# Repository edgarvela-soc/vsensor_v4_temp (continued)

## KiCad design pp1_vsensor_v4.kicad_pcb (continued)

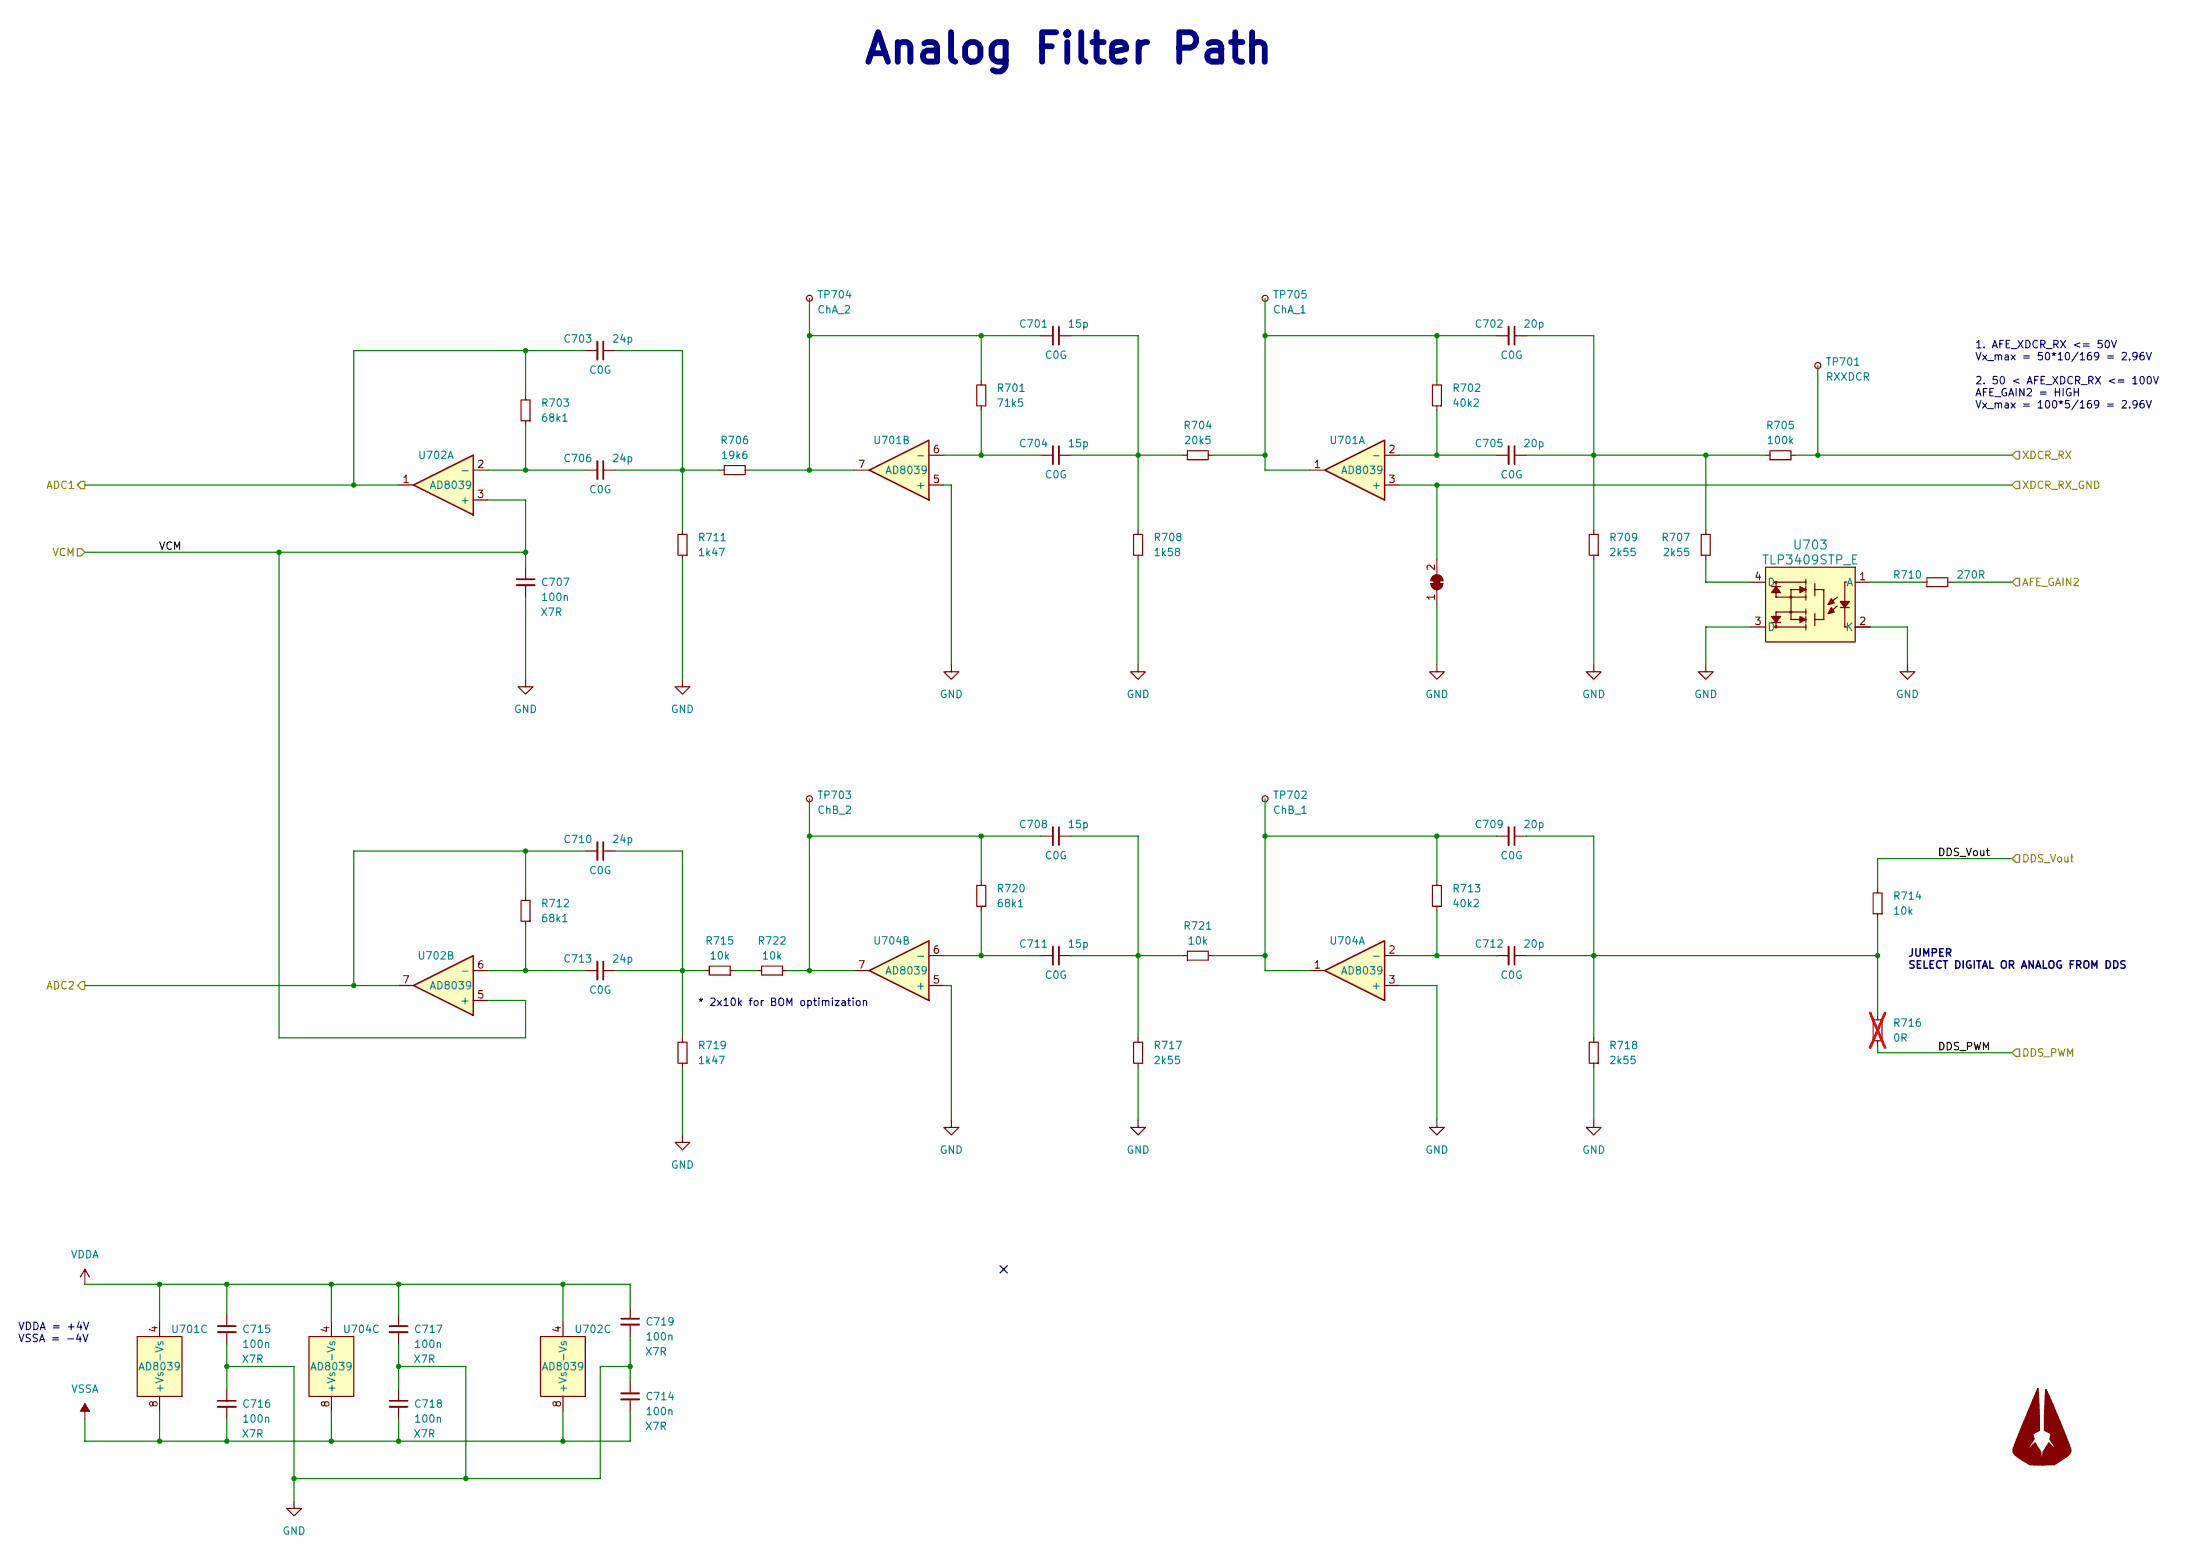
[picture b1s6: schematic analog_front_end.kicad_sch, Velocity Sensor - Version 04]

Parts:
C701, C704, C708, C711: 15p; C_0402_1005Metric; MPN CC0402JRNPO9BN150; Digikey_PN 311-1017-1-ND
C702, C705, C709, C712: 20p; C_0402_1005Metric; MPN CC0402JRNPO9BN200; Digikey_PN 311-1417-1-ND
C703, C706, C710, C713: 24p; C_0402_1005Metric; MPN CC0402JRNPO9BN240; Digikey_PN 311-1348-1-ND
C707, C714, C715, C716, C717, C718, C719: 100n; C_0402_1005Metric; Voltage 50V; MPN CC0402KRX7R9BB104; Digikey_PN 311-3566-1-ND
JP701: Bridged; NetTie-2_SMD_Pad0.5mm
Logo701: LOGO_AGU; AGU_15mm
R701: 71k5; R_0402_1005Metric; MPN RC0402FR-0771K5L; Digikey_PN YAG3222CT-ND
R702, R713: 40k2; R_0402_1005Metric; MPN RC0402FR-0740K2L; Digikey_PN 311-40.2KLRCT-ND
R703, R712, R720: 68k1; R_0402_1005Metric; MPN RC0402FR-0768K1L; Digikey_PN YAG3213CT-ND
R704: 20k5; R_0402_1005Metric; MPN RC0402FR-0720K5L; Digikey_PN YAG3052CT-ND
R705: 100k; R_0603_1608Metric; MPN RC0402FR-07100KL; Digikey_PN 311-100KLRCT-ND
R706: 19k6; R_0402_1005Metric; MPN RC0402FR-0719K6L; Digikey_PN YAG3026CT-ND
R707, R709, R717, R718: 2k55; R_0402_1005Metric; MPN RC0402FR-072K55L; Digikey_PN YAG3102CT-ND
R708: 1k58; R_0402_1005Metric; MPN RC0402FR-071K58L; Digikey_PN YAG3041CT-ND
R710: 270R; R_0402_1005Metric; MPN RMCF0402FT270R; Digikey_PN RMCF0402FT270RCT-ND
R711, R719: 1k47; R_0402_1005Metric; MPN RC0402FR-071K47L; Digikey_PN YAG3038CT-ND
R714, R715, R721, R722: 10k; R_0402_1005Metric; MPN RC1005F103CS; Digikey_PN 1276-3431-1-ND
R716: 0R; R_0402_1005Metric; MPN RC0402JR-070RL; Digikey_PN 311-0.0JRCT-ND; not fitted
TP701: RXXDCR; TestPoint_Pad_D1.0mm
TP702: ChB_1; TestPoint_Pad_D1.0mm
TP703: ChB_2; TestPoint_Pad_D1.0mm
TP704: ChA_2; TestPoint_Pad_D1.0mm
TP705: ChA_1; TestPoint_Pad_D1.0mm
U701, U702, U704: AD8039; SOT-23-8; MPN AD8039ARTZ-REEL7; Digikey_PN 505-AD8039ARTZ-REEL7CT-ND
U703: TLP3409STP_E; MPN TLP3409S(TP,E; Mouser_PN 757-TLP3409STPE

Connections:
/ADC/ADC1: C703.2, R703.2, U702.1; also elsewhere on the board
/ADC/ADC2: C710.2, R712.2, U702.7; also elsewhere on the board
/ADC/VCM: C707.1, U702.3 (+), U702.5 (+); also elsewhere on the board
/Analog Frontend/DDS_PWM: R716.1; also elsewhere on the board
/Analog Frontend/DDS_Vout: R714.2; also elsewhere on the board
/Microcontroller/AFE_GAIN2: R710.2; also elsewhere on the board
/Transducer Multiplexer/MUX_XDCR: R705.2, TP701.1; also elsewhere on the board
unnamed: C701.1, C704.1, R704.1, R708.2
unnamed: C701.2, R701.2, R706.2, TP704.1, U701.7
unnamed: C702.1, C705.1, R705.1, R707.2, R709.2
unnamed: C702.2, R702.2, R704.2, TP705.1, U701.1
unnamed: C703.1, C706.1, R706.1, R711.2
unnamed: C708.1, C711.1, R717.2, R721.1
unnamed: C708.2, R720.2, R722.1, TP703.1, U704.7
unnamed: C709.1, C712.1, R714.1, R716.2, R718.2
unnamed: C709.2, R713.2, R721.2, TP702.1, U704.1
unnamed: C710.1, C713.1, R715.2, R719.2
unnamed: R707.1, U703.4 (D)
unnamed: R715.1, R722.2
unnamed: C705.2, R702.1, U701.2 (-)
unnamed: C704.2, R701.1, U701.6 (-)
unnamed: C706.2, R703.1, U702.2 (-)
unnamed: C713.2, R712.1, U702.6 (-)
unnamed: R710.1, U703.1 (A)
unnamed: C712.2, R713.1, U704.2 (-)
unnamed: C711.2, R720.1, U704.6 (-)
VDDA: C715.1, C717.1, C719.1, U701.4 (-Vs), U702.4 (-Vs), U704.4 (-Vs); also elsewhere on the board
VSSA: C714.2, C716.2, C718.2, U701.8 (+Vs), U702.8 (+Vs), U704.8 (+Vs); also elsewhere on the board

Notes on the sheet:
1. AFE_XDCR_RX <= 50V Vx_max = 50*10/169 = 2.96V 2. 50 < AFE_XDCR_RX <= 100V AFE_GAIN2 = HIGH Vx_max = 100*5/169 = 2.96V
JUMPER SELECT DIGITAL OR ANALOG FROM DDS
* 2x10k for BOM optimization
VDDA = +4V VSSA = -4V
Analog Filter Path

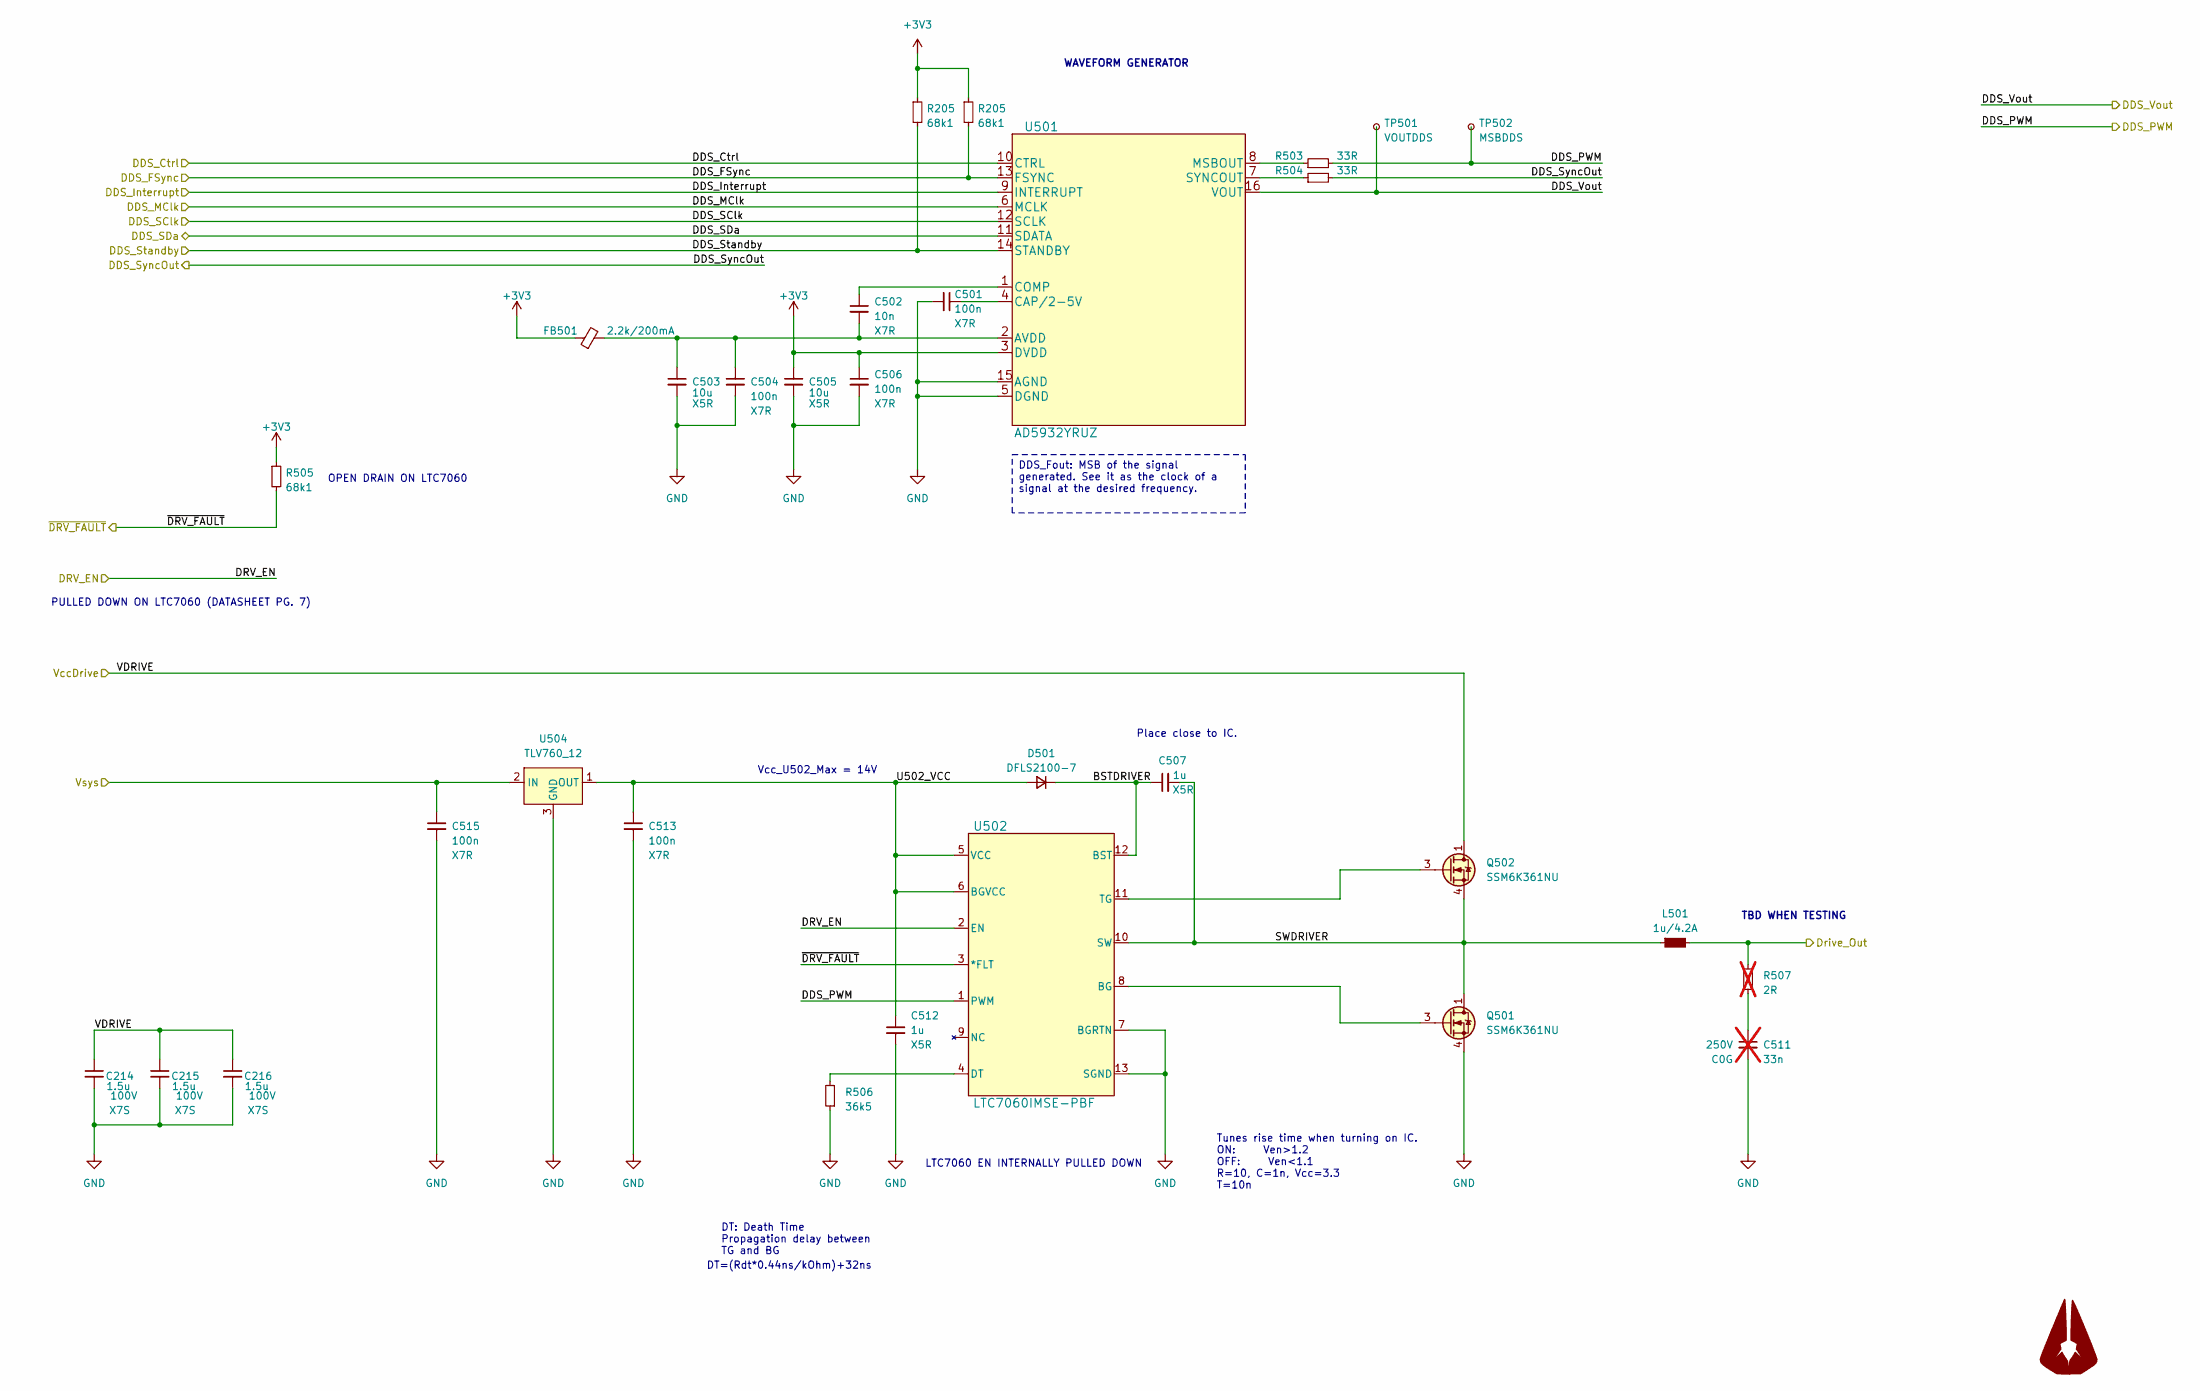
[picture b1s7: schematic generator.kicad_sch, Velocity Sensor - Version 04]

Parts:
C214, C215, C216: 1.5u; C_1206_3216Metric; Voltage 100V; MPN C3216X7S2A155K160AB; Mouser_PN 810-C3216X7S2A155K1B
C501, C504, C506, C513, C515: 100n; C_0402_1005Metric; Voltage 50V; MPN CC0402KRX7R9BB104; Digikey_PN 311-3566-1-ND
C502: 10n; C_0402_1005Metric; Voltage 50V; MPN GCM155R71H103KA55D; Digikey_PN 399-C0402C222J5RAC7867CT-ND
C503, C505: 10u; C_0603_1608Metric; Voltage 25V; MPN GRM188R61E106MA73D; Mouser_PN 81-GRM188R61E106MA3D
C507, C512: 1u; C_0402_1005Metric; Voltage 50V; MPN UMK105CBJ105MV-F; Digikey_PN 587-6278-1-ND
C511: 33n; C_0805_2012Metric; Voltage 250V; MPN 885342206005; Digikey_PN 732-12160-1-ND; not fitted
D501: DFLS2100-7; D_PowerDI-123; MPN DFLS2100-7; Mouser_PN 621-DFLS2100-7
FB501: 2.2k/200mA; L_0805_2012Metric; MPN 742792093; Digikey_PN 732-1609-1-ND
L501: 1u/4.2A; RES_CIGT201610; MPN CIGT201610EH1R0MNE; Digikey_PN 1276-6900-1-ND
Logo501: LOGO_AGU; AGU_15mm
Q501, Q502: SSM6K361NU; UDFN6B_TOS; MPN SSM6K361NU,LF; Digikey_PN SSM6K361NULFCT-ND
R205, R505: 68k1; R_0402_1005Metric; MPN RC0402FR-0768K1L; Digikey_PN YAG3213CT-ND
R503, R504: 33R; R_0402_1005Metric; MPN RC0402JR-0733RL; Digikey_PN 311-33JRCT-ND
R506: 36k5; R_0402_1005Metric; MPN ERJ-2RKF3652X; Digikey_PN P36.5KLCT-ND
R507: 2R; R_0805_2012Metric; MPN RMCF0603FT2R00; Digikey_PN RMCF0603FT2R00CT-ND; not fitted
TP501: VOUTDDS; TestPoint_Pad_D1.0mm
TP502: MSBDDS; TestPoint_Pad_D1.0mm
U501: AD5932YRUZ; MPN AD5932YRUZ; Mouser_PN 584-AD5932YRUZ
U502: LTC7060IMSE-PBF; LTC7060; MPN LTC7060IMSE#WTRPBF; Mouser_PN 584-7060IMSE#WTRPBF
U504: TLV760_12; SOT-23; MPN TLV76012DBZR; Digikey_PN 296-48331-1-ND

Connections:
+3V3: C505.1, C506.1, FB501.1, R505.1, U501.3 (DVDD); also elsewhere on the board
/Analog Frontend/DDS_PWM: R503.2, TP502.1, U502.1 (PWM); also elsewhere on the board
/Analog Frontend/DDS_Vout: TP501.1, U501.16 (VOUT); also elsewhere on the board
/Microcontroller/DDS_Ctrl: U501.10 (CTRL); also elsewhere on the board
/Microcontroller/DDS_FSync: U501.13 (FSYNC); also elsewhere on the board
/Microcontroller/DDS_INTERRUPT: U501.9 (INTERRUPT); also elsewhere on the board
/Microcontroller/DDS_MClk: U501.6 (MCLK); also elsewhere on the board
/Microcontroller/DDS_SClk: U501.12 (SCLK); also elsewhere on the board
/Microcontroller/DDS_SYNCOUT: R504.2; also elsewhere on the board
/Microcontroller/DDS_Sda: U501.11 (SDATA); also elsewhere on the board
/Microcontroller/DDS_Standby: U501.14 (STANDBY); also elsewhere on the board
/Microcontroller/DRIVE_EN: U502.2 (EN); also elsewhere on the board
/Microcontroller/~DRV_FAULT: R505.2, U502.3 (*FLT); also elsewhere on the board
/Signal Generator/BSTDRIVER: C507.1, D501.1 (K), U502.12 (BST)
/Signal Generator/SWDRIVER: C507.2, L501.1, Q501.1 (D), Q501.2 (D), Q501.5 (D), Q501.6 (D), Q501.7 (D), Q502.4 (S), Q502.8 (S), U502.10 (SW)
/Signal Generator/U502_VCC: C512.1, C513.1, D501.2 (A), U502.5 (VCC), U502.6 (BGVCC), U504.1 (OUT)
/Transducer Multiplexer/MUX_XDCR: L501.2, R507.2; also elsewhere on the board
unnamed: C511.1, R507.1
unnamed: Q501.3 (G), U502.8 (BG)
unnamed: Q502.3 (G), U502.11 (TG)
unnamed: C502.2, C503.1, C504.1, FB501.2, U501.2 (AVDD)
unnamed: C501.1, U501.4 (CAP/2-5V)
unnamed: C502.1, U501.1 (COMP)
unnamed: R503.1, U501.8 (MSBOUT)
unnamed: R504.1, U501.7 (SYNCOUT)
unnamed: R506.2, U502.4 (DT)

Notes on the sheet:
DDS_Fout: MSB of the signal generated. See it as the clock of a signal at the desired frequency.
Place close to IC.
Tunes rise time when turning on IC. ON: Ven>1.2 OFF: Ven<1.1 R=10, C=1n, Vcc=3.3 T=10n
OPEN DRAIN ON LTC7060
TBD WHEN TESTING
LTC7060 EN INTERNALLY PULLED DOWN
WAVEFORM GENERATOR
DT=(Rdt*0.44ns/kOhm)+32ns
PULLED DOWN ON LTC7060 (DATASHEET PG. 7)
DT: Death Time Propagation delay between TG and BG
Vcc_U502_Max = 14V

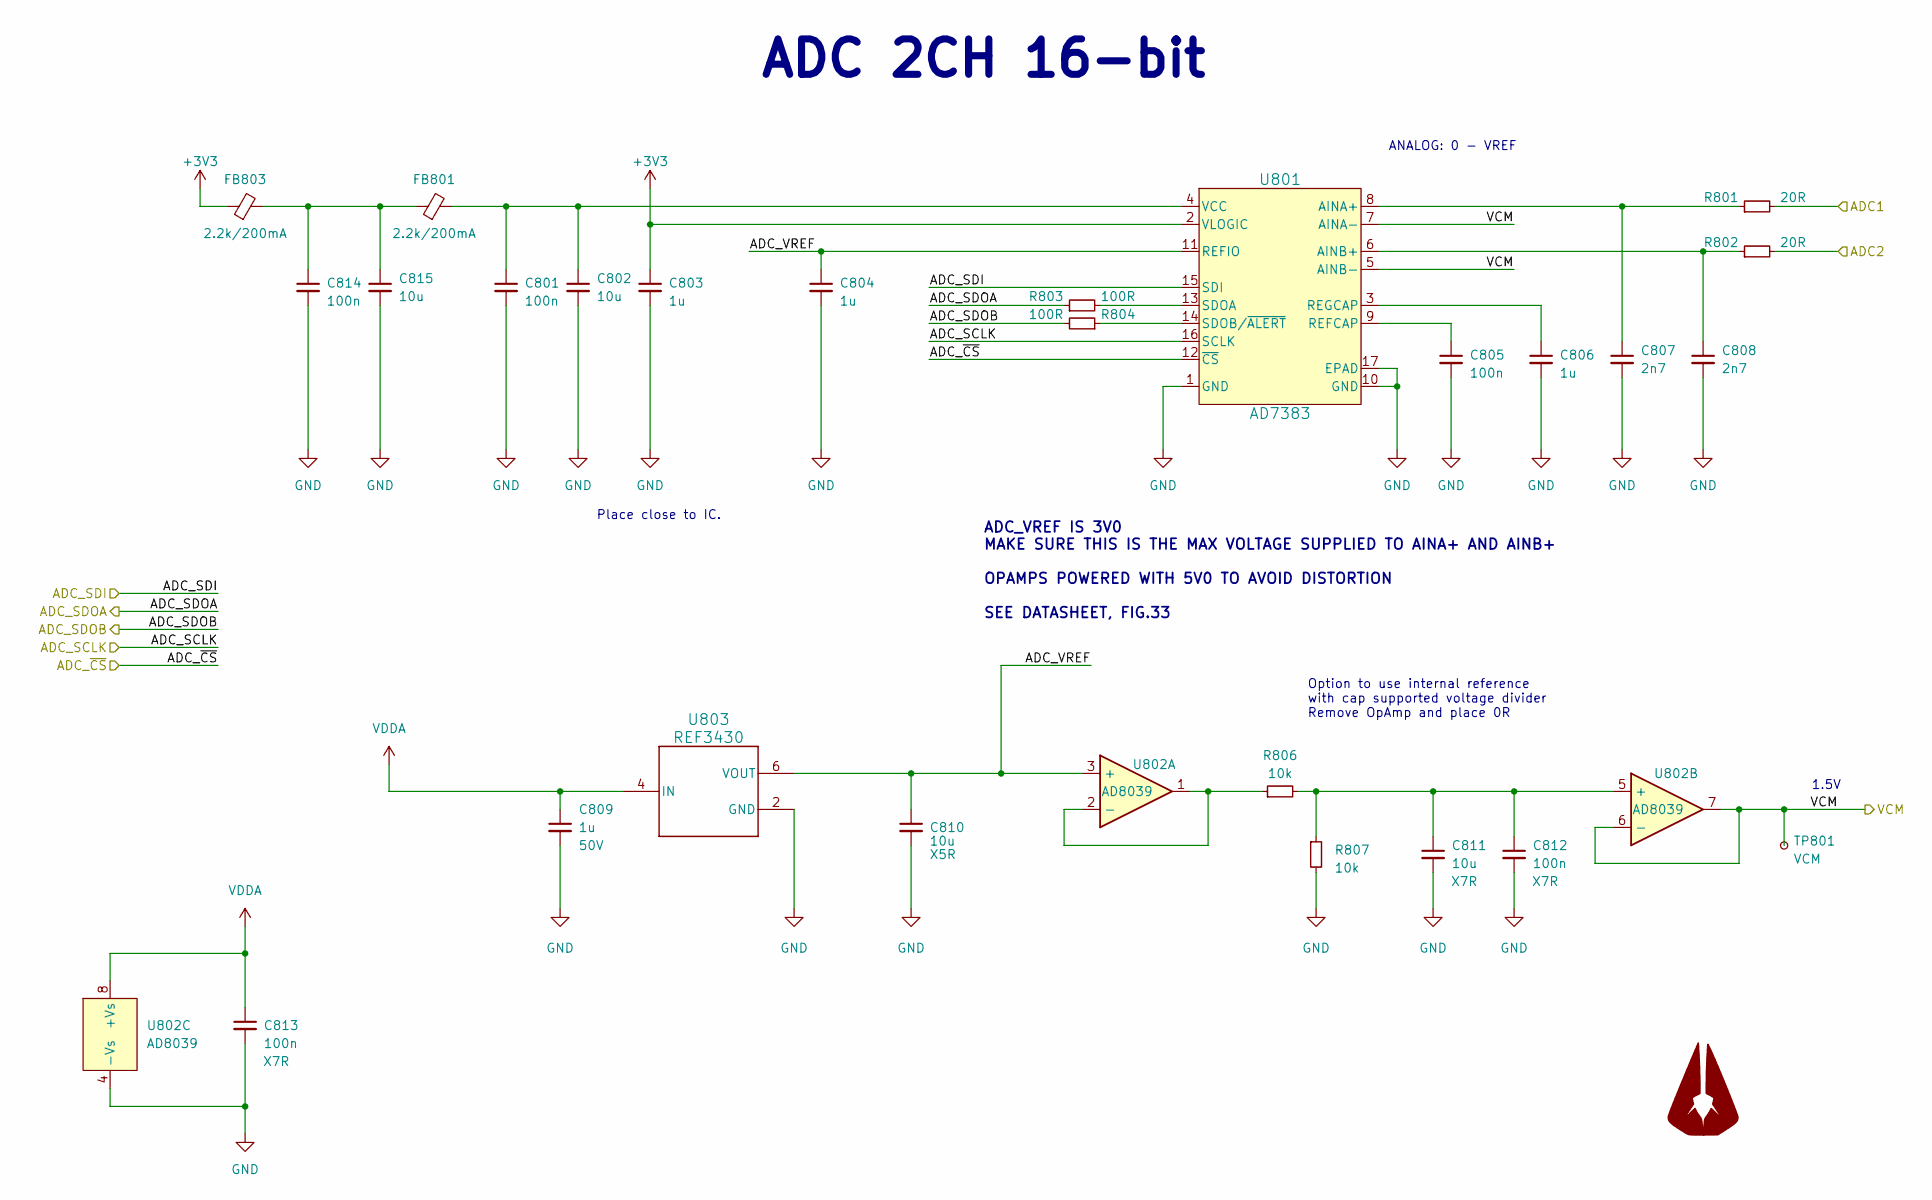
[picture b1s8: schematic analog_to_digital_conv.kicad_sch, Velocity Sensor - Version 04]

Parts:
C801, C805, C812, C813, C814: 100n; C_0402_1005Metric; Voltage 50V; MPN CC0402KRX7R9BB104; Digikey_PN 311-3566-1-ND
C802, C815: 10u; C_0603_1608Metric; Voltage 25V; MPN GRM188R61E106MA73D; Digikey_PN 490-7202-1-ND
C803, C804, C806: 1u; C_0603_1608Metric; MPN 06035C105KAT2A; Digikey_PN 478-10073-1-ND
C807, C808: 2n7; C_0603_1608Metric; MPN CC0603KRX7R9BB272; Digikey_PN 311-1809-1-ND
C809: 1u; C_0402_1005Metric; Voltage 50V; MPN UMK105CBJ105MV-F; Digikey_PN 587-6278-1-ND
C810, C811: 10u; C_0603_1608Metric; Voltage 25V; MPN GRM188R61E106MA73D; Mouser_PN 81-GRM188R61E106MA3D
FB801, FB803: 2.2k/200mA; L_0805_2012Metric; MPN 742792093; Digikey_PN 732-1609-1-ND
Logo801: LOGO_AGU; AGU_15mm
R801, R802: 20R; R_0402_1005Metric; MPN RC0402FR-0720RL; Digikey_PN 311-20LRCT-ND
R803, R804: 100R; R_0402_1005Metric; MPN RC0402FR-07100RL; Digikey_PN 311-100LRCT-ND
R806, R807: 10k; R_0402_1005Metric; MPN RC1005F103CS; Digikey_PN 1276-3431-1-ND
TP801: VCM; TestPoint_Pad_D1.0mm
U801: AD7383; MPN AD7383BCPZ-RL7; Digikey_PN 505-AD7383BCPZ-RL7CT-ND
U802: AD8039; SOT-23-8; MPN AD8039ARTZ-REEL7; Digikey_PN 505-AD8039ARTZ-REEL7CT-ND
U803: REF3430; MPN REF3430TIDBVR; Digikey_PN 296-REF3430TIDBVRCT-ND

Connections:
+3V3: C803.1, FB803.1, U801.2 (VLOGIC); also elsewhere on the board
/ADC/ADC1: R801.2; also elsewhere on the board
/ADC/ADC2: R802.2; also elsewhere on the board
/ADC/ADC_SCLK: U801.16 (SCLK); also elsewhere on the board
/ADC/ADC_SDI: U801.15 (SDI); also elsewhere on the board
/ADC/ADC_SDOA: R803.1; also elsewhere on the board
/ADC/ADC_SDOB: R804.2; also elsewhere on the board
/ADC/ADC_VREF: C804.1, C810.1, U801.11 (REFIO), U802.3 (+), U803.6 (VOUT)
/ADC/ADC_~CS: U801.12 (~CS); also elsewhere on the board
/ADC/VCM: TP801.1, U801.5 (AINB-), U801.7 (AINA-), U802.6 (-), U802.7; also elsewhere on the board
unnamed: C814.1, C815.1, FB801.1, FB803.2
unnamed: C807.1, R801.1, U801.8 (AINA+)
unnamed: C808.1, R802.1, U801.6 (AINB+)
unnamed: C805.1, U801.9 (REFCAP)
unnamed: C806.1, U801.3 (REGCAP)
unnamed: R803.2, U801.13 (SDOA)
unnamed: R804.1, U801.14 (SDOB/~ALERT)
unnamed: C801.1, C802.1, FB801.2, U801.4 (VCC)
unnamed: R806.1, U802.1, U802.2 (-)
unnamed: C811.1, C812.1, R806.2, R807.1, U802.5 (+)
VDDA: C809.1, C813.1, U802.8 (+Vs), U803.1 (NC), U803.3 (NC), U803.4 (IN), U803.5 (NC); also elsewhere on the board

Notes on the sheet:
ADC_VREF IS 3V0 MAKE SURE THIS IS THE MAX VOLTAGE SUPPLIED TO AINA+ AND AINB+ OPAMPS POWERED WITH 5V0 TO AVOID DISTORTION SEE DATASHEET, FIG.33
ADC 2CH 16-bit
Option to use internal reference with cap supported voltage divider Remove OpAmp and place 0R
Place close to IC.
ANALOG: 0 - VREF
1.5V

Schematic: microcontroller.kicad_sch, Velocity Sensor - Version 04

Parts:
C221: 1u; C_0402_1005Metric; Voltage 50V; MPN UMK105CBJ105MV-F; Digikey_PN 587-6278-1-ND
C401, C402: 9p; C_0402_1005Metric; MPN GRM1555C1H9R0BA01D; Digikey_PN 490-6257-1-ND
C403, C404, C405, C406, C407, C408, C409, C410, C411, C412, C419: 100n; C_0402_1005Metric; Voltage 50V; MPN CC0402KRX7R9BB104; Digikey_PN 311-3566-1-ND
C413: 4u7; C_0402_1005Metric; Voltage 25V; MPN 04023D475MAT2A; Digikey_PN 478-04023D475MAT2ACT-ND
C415: 220p; C_0402_1005Metric; Voltage 50V; MPN 0402N221J500CT; Digikey_PN 1292-1286-1-ND
C416, C421: 10u; C_0603_1608Metric; Voltage 25V; MPN GRM188R61E106MA73D; Mouser_PN 81-GRM188R61E106MA3D
L401: 2.2u; Inductor_0806; MPN DFE201612PD-2R2M=P2; Mouser_PN 81-DFE201612PD2R2P2
Logo401: LOGO_AGU; AGU_15mm
R401: 10k; R_0402_1005Metric; MPN RC1005F103CS; Digikey_PN 1276-3431-1-ND
R402, R403, R404, R405, R406, R407, R408, R409, R410, R411, R412, R413: 33R; R_0402_1005Metric; MPN RC0402JR-0733RL; Digikey_PN 311-33JRCT-ND
TP401: VFBSMPS; TestPoint_Pad_D1.0mm
U401: STM32H725IGK6; UFBGA-201_10x10mm_Layout15x15_P0.65mm; MPN STM32H725IGK6; Digikey_PN 497-STM32H725IGK6-ND
U402: S70KL1282; S27KS0642GABHV020; MPN S70KL1282GABHV020; Digikey_PN 448-S70KL1282GABHV020-ND
Y401: ECX-1637_25MHz; XTAL_ECS-160-9-37-CKM-TR; MPN ECS-250-8-37-RWN-TR; Digikey_PN XC2484CT-ND

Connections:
+3V3: C403.1, C404.1, C405.1, C406.1, C407.1, C408.1, C409.1, C410.1, C411.1, C412.1, C413.1, C419.1, U401.D4 (PDR_ON), U401.D5 (VDD), U401.D11 (VDD), U401.E2 (VBAT), U401.E4 (VDD), U401.E12 (VDD), U401.E15 (VDD50USB), U401.F13 (VDD33USB), U401.G1 (VDDSMPS), U401.G4 (VDD), U401.H12 (VDD), U401.K4 (VDD), U401.L12 (VDD), U401.M5 (VDD), U401.M9 (VDD), U402.B4 (VCC), U402.D1 (VCCQ), U402.E4 (VCCQ); also elsewhere on the board
/ADC/ADC_SCLK: U401.N5 (PA3), U401.N12 (PB10), U401.P12 (PE12); also elsewhere on the board
/ADC/ADC_SDI: U401.M1 (PC2); also elsewhere on the board
/ADC/ADC_SDOA: U401.M2 (PC3); also elsewhere on the board
/ADC/ADC_SDOB: U401.D3 (PE5); also elsewhere on the board
/ADC/ADC_~CS: U401.B1 (PE4), U401.B3 (PB9), U401.P1 (PA0); also elsewhere on the board
/High Voltage Supply/VSel0: U401.G13 (PG7); also elsewhere on the board
/High Voltage Supply/VSel1: U401.G12 (PG8); also elsewhere on the board
/High Voltage Supply/VSel2: U401.P9 (PE7)
/Interface/SD_CLK: U401.B11 (PC12); also elsewhere on the board
/Interface/SD_CMD: U401.B10 (PD2); also elsewhere on the board
/Interface/SD_D0: U401.D14 (PC8); also elsewhere on the board
/Interface/SD_D1: U401.E13 (PC9); also elsewhere on the board
/Interface/SD_D2: U401.C12 (PC10); also elsewhere on the board
/Interface/SD_D3: U401.C11; also elsewhere on the board
/Interface/SD_DETECT: U401.B15 (PA12); also elsewhere on the board
/Interface/VSENS_D0: U401.M14 (PH9); also elsewhere on the board
/Interface/VSENS_D1: U401.J15 (PD12); also elsewhere on the board
/Interface/VSENS_D2: U401.C4 (PE1); also elsewhere on the board
/Interface/VSENS_D3: U401.R2 (PA2); also elsewhere on the board
/Interface/VSENS_D4: U401.P15 (PH6); also elsewhere on the board
/Interface/VSENS_SWCLK: U401.A12 (PA14(JTCK); also elsewhere on the board
/Interface/VSENS_SWDIO: U401.B13 (PA13(JTMS); also elsewhere on the board
/Interface/VSENS_uc_RX: U401.H14 (PD14); also elsewhere on the board
/Interface/VSENS_uc_TX: U401.J12 (PD15); also elsewhere on the board
/Interface/nRST: R411.1, U401.L1 (NRST); also elsewhere on the board
/Microcontroller/AFE_GAIN2: U401.D1 (PC15); also elsewhere on the board
/Microcontroller/DDS_Ctrl: U401.N14 (PH10); also elsewhere on the board
/Microcontroller/DDS_FSync: U401.P5 (PA4); also elsewhere on the board
/Microcontroller/DDS_INTERRUPT: U401.R7 (PA6); also elsewhere on the board
/Microcontroller/DDS_MClk: U401.B14 (PA8); also elsewhere on the board
/Microcontroller/DDS_SClk: U401.B7 (PG13); also elsewhere on the board
/Microcontroller/DDS_SYNCOUT: U401.D15 (PC7); also elsewhere on the board
/Microcontroller/DDS_Sda: U401.N6 (PA7); also elsewhere on the board
/Microcontroller/DDS_Standby: U401.C15 (PA11); also elsewhere on the board
/Microcontroller/DRIVE_EN: U401.N7 (PF11); also elsewhere on the board
/Microcontroller/HV_ENABLE: U401.M13 (PH11); also elsewhere on the board
/Microcontroller/Rx_Ena: U401.D2 (PC14); also elsewhere on the board
/Microcontroller/SD_EN3V3: U401.C13 (PH13); also elsewhere on the board
/Microcontroller/VDDA: U401.M3 (VREF+), U401.M4 (VDDA)
/Microcontroller/VFBSMPS: C416.1, C421.1, L401.2, TP401.1, U401.A3 (VDDLDO), U401.A4 (VCAP), U401.A13 (VDDLDO), U401.A14 (VCAP), U401.G2 (VFBSMPS), U401.R13 (VCAP), U401.R14 (VDDLDO)
/Microcontroller/VLXSMPS: C415.1, L401.1, U401.F1 (VLXSMPS)
/Microcontroller/XDCR_Sel1: U401.R12 (PE11); also elsewhere on the board
/Microcontroller/XDCR_Sel2: U401.R11 (PE9); also elsewhere on the board
/Microcontroller/XDCR_Sel3: U401.R10 (PF14); also elsewhere on the board
/Microcontroller/XDCR_Sel4: U401.R9 (PE10); also elsewhere on the board
/Microcontroller/dram_ck: R413.2, U402.B2 (CK)
/Microcontroller/dram_dq0: R403.2, U402.D3 (DQ0)
/Microcontroller/dram_dq1: R404.2, U402.D2 (DQ1)
/Microcontroller/dram_dq2: R405.2, U402.C4 (DQ2)
/Microcontroller/dram_dq3: R406.2, U402.D4 (DQ3)
/Microcontroller/dram_dq4: R407.2, U402.D5 (DQ4)
/Microcontroller/dram_dq5: R408.2, U402.E3 (DQ5)
/Microcontroller/dram_dq6: R409.2, U402.E2 (DQ6)
/Microcontroller/dram_dq7: R410.2, U402.E1 (DQ7)
/Microcontroller/dram_nrst: R411.2, U402.A4 (~RESET)
/Microcontroller/dram_rwds: R412.2, U402.C3 (RWDS)
/Microcontroller/uC_dram_ck: R413.1, U401.H2 (PF4)
/Microcontroller/uC_dram_dq0: R403.1, U401.F4 (PF0)
/Microcontroller/uC_dram_dq1: R404.1, U401.F3 (PF1)
/Microcontroller/uC_dram_dq2: R405.1, U401.G3 (PF2)
/Microcontroller/uC_dram_dq3: R406.1, U401.H4 (PF3)
/Microcontroller/uC_dram_dq4: R407.1, U401.P8 (PG0)
/Microcontroller/uC_dram_dq5: R408.1, U401.N9 (PG1)
/Microcontroller/uC_dram_dq6: R409.1, U401.C8 (PG10)
/Microcontroller/uC_dram_dq7: R410.1, U401.A7 (PG11)
/Microcontroller/uC_dram_rwds: R412.1, U401.D7 (PG15)
/Microcontroller/~DRV_FAULT: U401.D13 (PA9); also elsewhere on the board
/Microcontroller/~uC_dram_CS: R402.1, U401.D8 (PG12)
unnamed: R401.2, U401.C5 (BOOT0)
unnamed: C402.1, U401.J1 (PH0), Y401.3
unnamed: C401.1, U401.K1 (PH1), Y401.1
unnamed: R402.2, U402.A3 (~CS)

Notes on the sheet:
SPI4_MISO
DFLT
VREF: 1 uF ceramic and 100 nF ceramic close to the pin or connected to VDDA through a resistor (typically 47Ohm)
MCO1
DI/INT
SPI6_SCK
SPI2_MISO
SPI4_SCLK
RESERVED
JTAG
RAM
SPI2_NSS
SD_D1
100nF ceramic for each VDD as close as possible to the pins. 4.7uF ceramic to one VDD.
SPI4_NSS
VDD33USB 0:3V6 When USB is not used, w/o external components.
PA0_C AND PA1_C: ONLY ANALOG DIRECT CH
SD_D2
TIM5_CH1
ANALOG
VDD50USB Connected to VDD33USB when the internal USB regulator is not used (for packages having this pin available).
SPI6_MOSI
SD_CMD
TABLE 16. DIRECT SMPS ONLY STM32H725xE/G
SPI6_~{SS}
SD_D0
ADC12_INP1
SPI2_SCLK
TIM2_CH1
DRAM 128Mbit HyperBus
TIM24_CH1
ADC12_INP0
TIM13_CH1
SD_D3
SD_CK
POWER SUPPLY CONNECTION (AN5419)
TIM15_CH2
TIM12_CH2
SPI2_MOSI

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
